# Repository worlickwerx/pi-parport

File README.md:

## pi-parport

This is a Raspberry Pi HAT that implements a PC-style parallel port.
GPIO pins are organized as data, status, and control registers.
The HAT includes a buffer chip that converts from the GPIB 3V3 logic
to signals that conform to IEEE 1284.  A 26 pin IDC header on the
board connects to your DB25 connector.  A `parport-gpio` driver and
device tree overlay integrate the HAT with the Linux parport driver stack.

### Why?

I wanted to use a parallel port based cooled astronomy camera,
but preferred to use the compact and low-power Raspberry Pi
over a PC at the telescope.  Parallel ports are simple devices.
Why not build one?

### What works?

See [wiki](https://github.com/worlickwerx/pi-parport/wiki) for notes on some
devices, and please share your experience if you try something new.

The following limitations of this implementation may affect software and
hardware that uses the parallel port:
1) The software cannot directly read and write the x86 port addresses,
as was the custom early on.  In user space, software must use the ppdev
ioctl interface.  In the kernel, software must use the (generic)
`struct parport` operations.
2) The GPIO multiplexing/de-multiplexing and/or system call access may
impact the direct-access latency assumed by some bit-banged drivers.
On a Pi 3, user space code can toggle a parallel port line at about 250 kHz.
3) Bidirectional control pins are not currently supported, but bidirectional
data pins are supported.  There are alternatives to the current buffer chip
that would support this, but they require a slightly more complicated
circuit.

### Why not use a USB Parallel Port?

Many USB parallel port devices appear to Linux as a USB printer, bypassing
the parport driver stack.  If your application is a printer, go for it.

### Building the driver

For convenience, the generic parport code is duplicated in this repo,
since the Raspberry Pi Foundation does not ship the compiled modules
in the `raspberrypi-kernel` package (at least in old Raspbian
versions).  If you are intending to use a specific old version of
Raspbian, there is the shell script `get_parport_src.sh` to assist
you in getting the code from that particular version.

Clone this repo, then run the following with `${TOPDIR}` representing the
top level directory of the cloned repo:
```console
$ sudo apt install build-essential raspberrypi-kernel-headers
$ cd ${TOPDIR}/driver
$ make
make -C /lib/modules/4.19.75-v7+/build M=${TOPDIR}/driver modules
make[1]: Entering directory '/usr/src/linux-headers-4.19.75-v7+'
  CC [M]  ${TOPDIR}/driver/parport/share.o
  CC [M]  ${TOPDIR}/driver/parport/ieee1284.o
  CC [M]  ${TOPDIR}/driver/parport/ieee1284_ops.o
  CC [M]  ${TOPDIR}/driver/parport/procfs.o
  CC [M]  ${TOPDIR}/driver/parport/daisy.o
  CC [M]  ${TOPDIR}/driver/parport/probe.o
  LD [M]  ${TOPDIR}/driver/parport/parport.o
  CC [M]  ${TOPDIR}/driver/parport/lp.o
  CC [M]  ${TOPDIR}/driver/parport/ppdev.o
  CC [M]  ${TOPDIR}/driver/parport_gpio.o
  Building modules, stage 2.
  MODPOST 4 modules
  CC      ${TOPDIR}/driver/parport/lp.mod.o
  LD [M]  ${TOPDIR}/driver/parport/lp.ko
  CC      ${TOPDIR}/driver/parport/parport.mod.o
  LD [M]  ${TOPDIR}/driver/parport/parport.ko
  CC      ${TOPDIR}/driver/parport/ppdev.mod.o
  LD [M]  ${TOPDIR}/driver/parport/ppdev.ko
  CC      ${TOPDIR}/driver/parport_gpio.mod.o
  LD [M]  ${TOPDIR}/driver/parport_gpio.ko
make[1]: Leaving directory '/usr/src/linux-headers-4.19.75-v7+'
```

### Installing the Device Tree Overlay

The device tree overlay maps specific GPIO pins to their functions in
the driver.  This must be compiled and loaded:
```console
$ cd ${TOPDIR}/dts
$ make
$ sudo make install
```
The ID EEPROM stores the name of the DT Overlay to use, and the
corresponding DT Overlay will be automatically loaded on boot.  If you
will not be using an ID EEPROM, then add the following line to
`/boot/config.txt`:
```
dtoverlay=parport-gpio
```
The default drive mode of the parallel port output pins is
"totem-pole" mode, which means that a high current source is provided
for both logic level 1 and 0.  If you wish logic level 1 to be a low
current source provided by pull-up resistors, i.e. "open-drain" mode,
then you can set the following DT Overlay parameter:
```
dtoverlay=parport-gpio,hd=0
```
Note that if you are using an EEPROM, you will have to include the
full DT Overlay data within your EEPROM since you cannot simply
specify a parameter when loading by that method.

Then reboot the pi to pick up the new config.

### Installing the Modules

Install the modules to allow Linux Device Tree to automatically load
them.
```console
$ cd ${TOPDIR}/driver
$ sudo make install
```
Note that only the `parport` and `parport_gpio` base modules will
autoload, the `ppdev` and `lp` modules will still need to be specified
in `/etc/modules` or otherwise.  Also, note that you will need to
rebuild and reinstall the modules when you update your kernel version.

### Loading the Modules

If you did not install the modules, after rebooting, load the base
modules like this:
```console
$ cd ${TOPDIR}
$ sudo insmod driver/parport/parport.ko
$ sudo insmod driver/parport_gpio.ko
```
You'll see the port announce itself on the console:
```console
[4425200.988400] parport-gpio ppgpio@0: data on pins [22,23,24,10,25,9,8,11]
[4425200.988412] parport-gpio ppgpio@0: status on pins [18,17,4,3,2]
[4425200.988422] parport-gpio ppgpio@0: control on pins [26,19,6,13]
[4425200.988430] parport-gpio ppgpio@0: hd on pin 20
[4425200.988438] parport-gpio ppgpio@0: dir on pin 21
```
If you wish to set up a parallel printer:
```console
$ sudo insmod parport/lp.ko
```
If you wish to run user-space programs that use the parallel port:
```console
$ sudo insmod parport/ppdev.ko
```

### hardware

The latest hardware includes an ID EEPROM to conform with the
[Raspberry Pi HAT Specification](https://github.com/raspberrypi/hats),
and was designed with [KiCAD](https://www.kicad.org/).
As with the previous versions, the
[SN74LVC161284 19-bit bus interface with 3-state outputs](http://www.ti.com/product/SN74LVC161284) takes care of buffering and line conditioning.

Version 4 is shared on
[OSHPARK](https://oshpark.com/shared_projects/0Ioh20Gk).
See the [Bill of Materials](hardware/v4/BOM.md) for parts to place on
the board.

Populating the EEPROM and associated components on a board you're making
yourself is optional.

Check out the [test](test/) directory for some simple "smoke tests"
on your assembled pi-parport board before attaching your more
expensive equipment.

Schematics and design files for [previous versions](hardware/)
are still available for reference.

### Release

Share and enjoy!

#### Software License

SPDX-License-Identifier: GPL-2.0-or-later

#### Hardware License

SPDX-License-Identifier: CERN-OHL-1.2

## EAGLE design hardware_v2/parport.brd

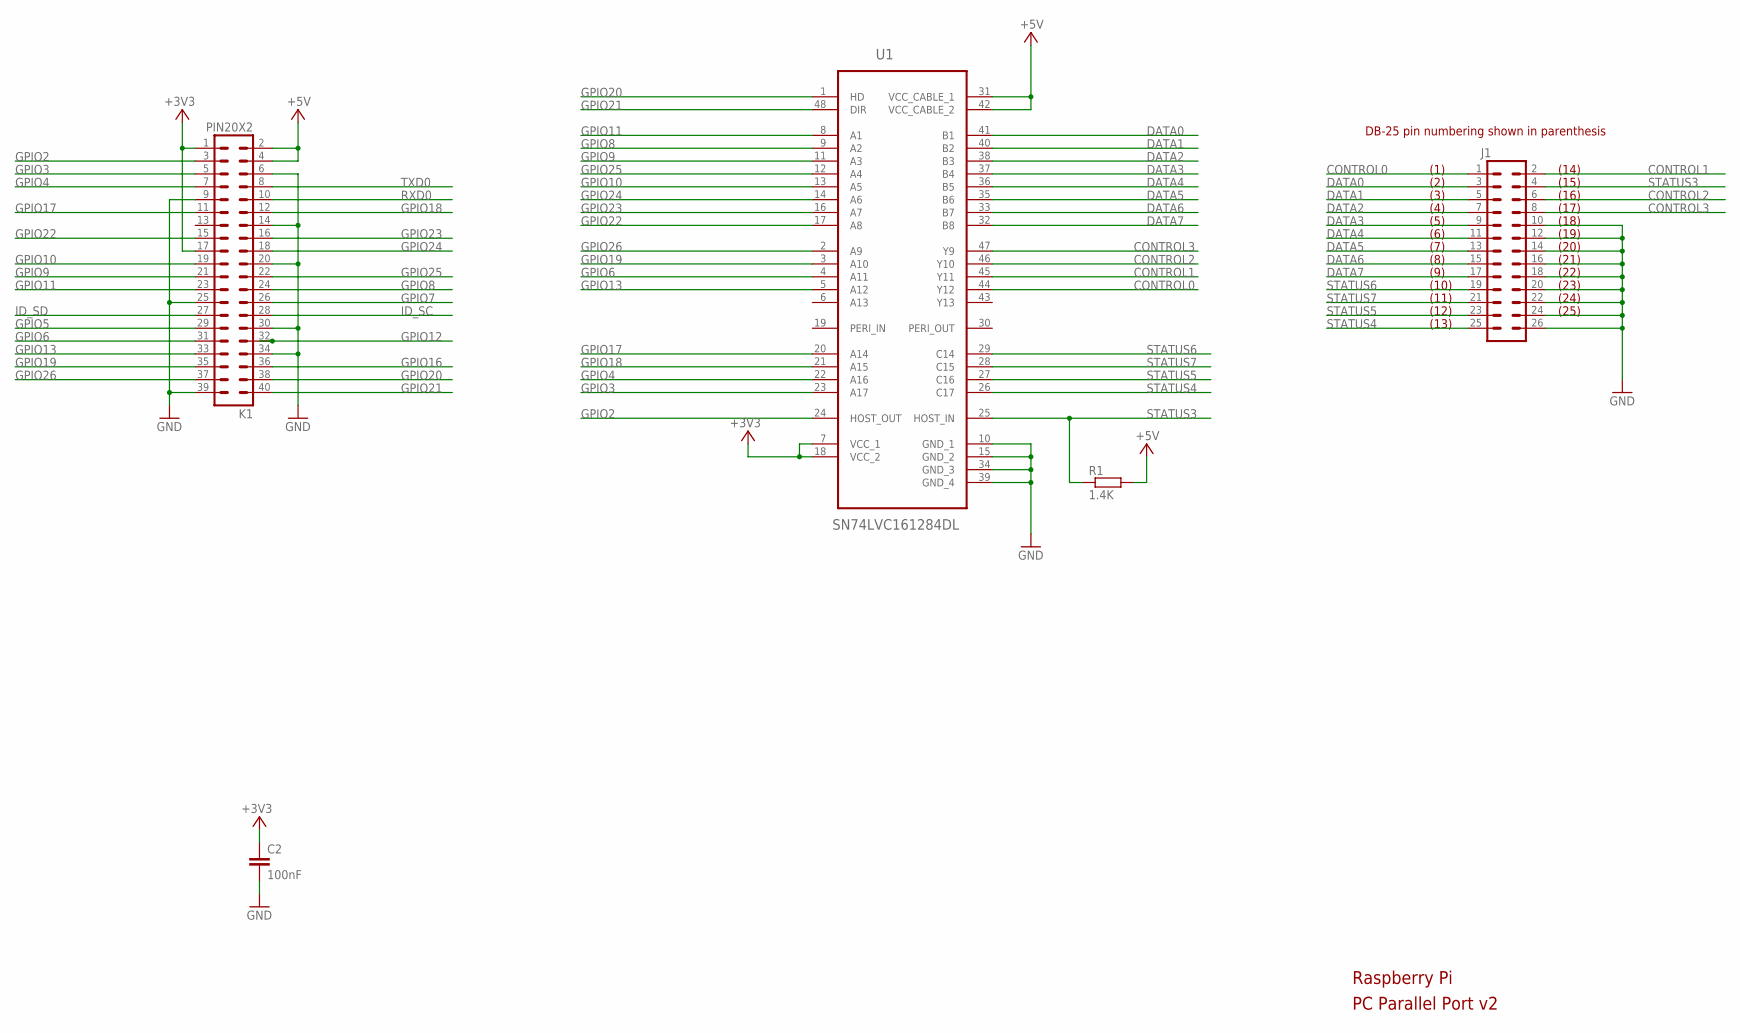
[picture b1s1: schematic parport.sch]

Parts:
C2: 100nF; C0805
J1: M13X22X13; 2X13
K1: PIN20X2; PIN_20X2
R1: 1.4K; R0805
U1: SN74LVC161284DL; SOP63P1035X279-48N

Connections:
+3V3: C2.1, K1.1, K1.17, U1.7 (VCC_1), U1.18 (VCC_2)
+5V: K1.2, K1.4, R1.2, U1.31 (VCC_CABLE_1), U1.42 (VCC_CABLE_2)
CONTROL0: J1.1, U1.44 (Y12)
CONTROL1: J1.2, U1.45 (Y11)
CONTROL2: J1.6, U1.46 (Y10)
CONTROL3: J1.8, U1.47 (Y9)
DATA0: J1.3, U1.41 (B1)
DATA1: J1.5, U1.40 (B2)
DATA2: J1.7, U1.38 (B3)
DATA3: J1.9, U1.37 (B4)
DATA4: J1.11, U1.36 (B5)
DATA5: J1.13, U1.35 (B6)
DATA6: J1.15, U1.33 (B7)
DATA7: J1.17, U1.32 (B8)
GND: C2.2, J1.10, J1.12, J1.14, J1.16, J1.18, J1.20, J1.22, J1.24, J1.26, K1.6, K1.9, K1.14, K1.20, K1.25, K1.30, K1.34, K1.39, U1.6 (A13), U1.10 (GND_1), U1.15 (GND_2), U1.19 (PERI_IN), U1.34 (GND_3), U1.39 (GND_4)
GPIO2: K1.3, U1.24 (HOST_OUT)
GPIO3: K1.5, U1.23 (A17)
GPIO4: K1.7, U1.22 (A16)
GPIO5: K1.29
GPIO6: K1.31, U1.4 (A11)
GPIO7: K1.26
GPIO8: K1.24, U1.9 (A2)
GPIO9: K1.21, U1.11 (A3)
GPIO10: K1.19, U1.13 (A5)
GPIO11: K1.23, U1.8 (A1)
GPIO12: K1.32
GPIO13: K1.33, U1.5 (A12)
GPIO16: K1.36
GPIO17: K1.11, U1.20 (A14)
GPIO18: K1.12, U1.21 (A15)
GPIO19: K1.35, U1.3 (A10)
GPIO20: K1.38, U1.1 (HD)
GPIO21: K1.40, U1.48 (DIR)
GPIO22: K1.15, U1.17 (A8)
GPIO23: K1.16, U1.16 (A7)
GPIO24: K1.18, U1.14 (A6)
GPIO25: K1.22, U1.12 (A4)
GPIO26: K1.37, U1.2 (A9)
ID_SC: K1.28
ID_SD: K1.27
RXD0: K1.10
STATUS3: J1.4, R1.1, U1.25 (HOST_IN)
STATUS4: J1.25, U1.26 (C17)
STATUS5: J1.23, U1.27 (C16)
STATUS6: J1.19, U1.29 (C14)
STATUS7: J1.21, U1.28 (C15)
TXD0: K1.8

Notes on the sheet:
Raspberry Pi
PC Parallel Port v2
(1)
(2)
(3)
(4)
(5)
(6)
(7)
(8)
(9)
(10)
(11)
(12)
(13)
(14)
(15)
(17)
(18)
(19)
(20)
(21)
(22)
(23)
(24)
(25)
(16)
DB-25 pin numbering shown in parenthesis

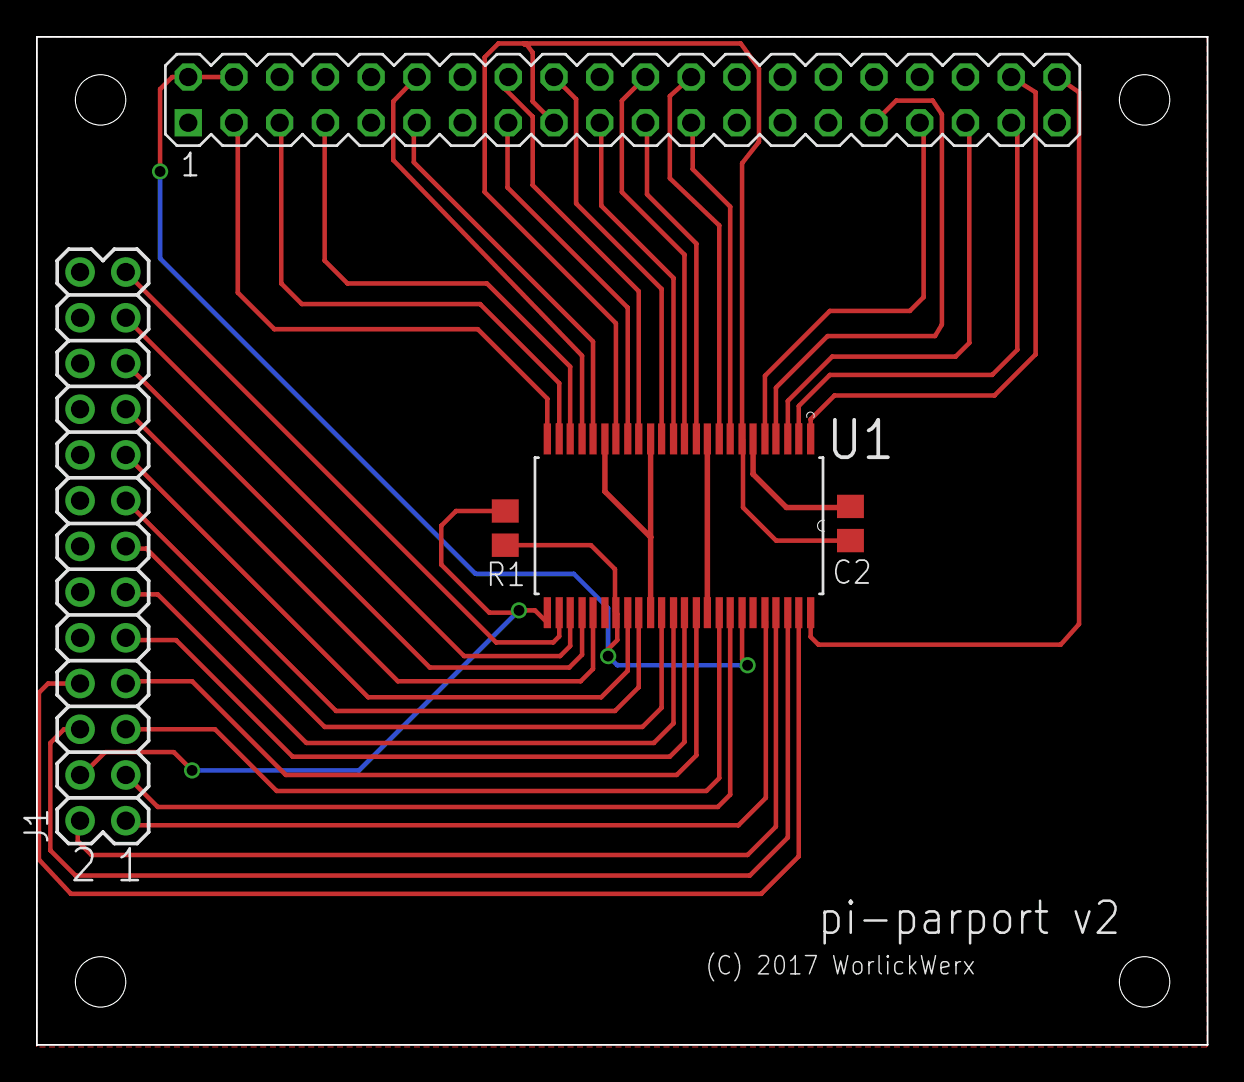
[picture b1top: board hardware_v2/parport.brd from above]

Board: 2 copper layers, 65.0 x 56.0 mm, 5 parts (0 on the bottom side), 39 nets.

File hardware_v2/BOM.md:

## hardware v2 bill of materials

| Quan | Part no | Manuf part no | Description | Package | Supplier | Notes |
| ---- | ------- | ------------- | ----------- | ------- | -------- | ----- |
| 1    | U1      | [SN74LVC161284DLR](http://www.ti.com/product/SN74LVC161284) | 19-bit bus interface with 3-state outputs | SSOP (0.64mm lead pitch) | [Arrow Electronics](https://www.arrow.com/en/products/sn74lvc161284dlr/texas-ins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 | pin 1 marking oriented opposite J1 |
| 1    | R1      |               | 1.4K ohm, 1/8 watt resistor              | 0805 |     | Pull-up for STATUS3 |
| 1    | C2      |               | 100nF, 50V capacitor                     | 0805 |     | Bypass |
| 1    | J1      |               | 13x2 male header                         | through-hole (2.54mm pitch) |    | Straight or 90 degree depending on application |
| 1    | K1      |               | 20x2 female header                       | through-hole (2.54mm pitch) | [Adafruit](https://www.adafruit.com/product/2222) | pi GPIO header |
| 4    |         |               | M2.5 x 16mm brass standoff, with M2.5 nut |                            | [Adafruit](https://www.adafruit.com/product/2336) | pi HAT standoff (height 11mm) |
| 4    |         |               | M2.5 x 6mm philips head screw            |     |    |    |
| 1    |         |               | Female DB25 to female 13x2 header cable assembly |     | [Amazon](https://www.amazon.com/Motherboard-Parallel-Printer-bracket-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 | or surplus |

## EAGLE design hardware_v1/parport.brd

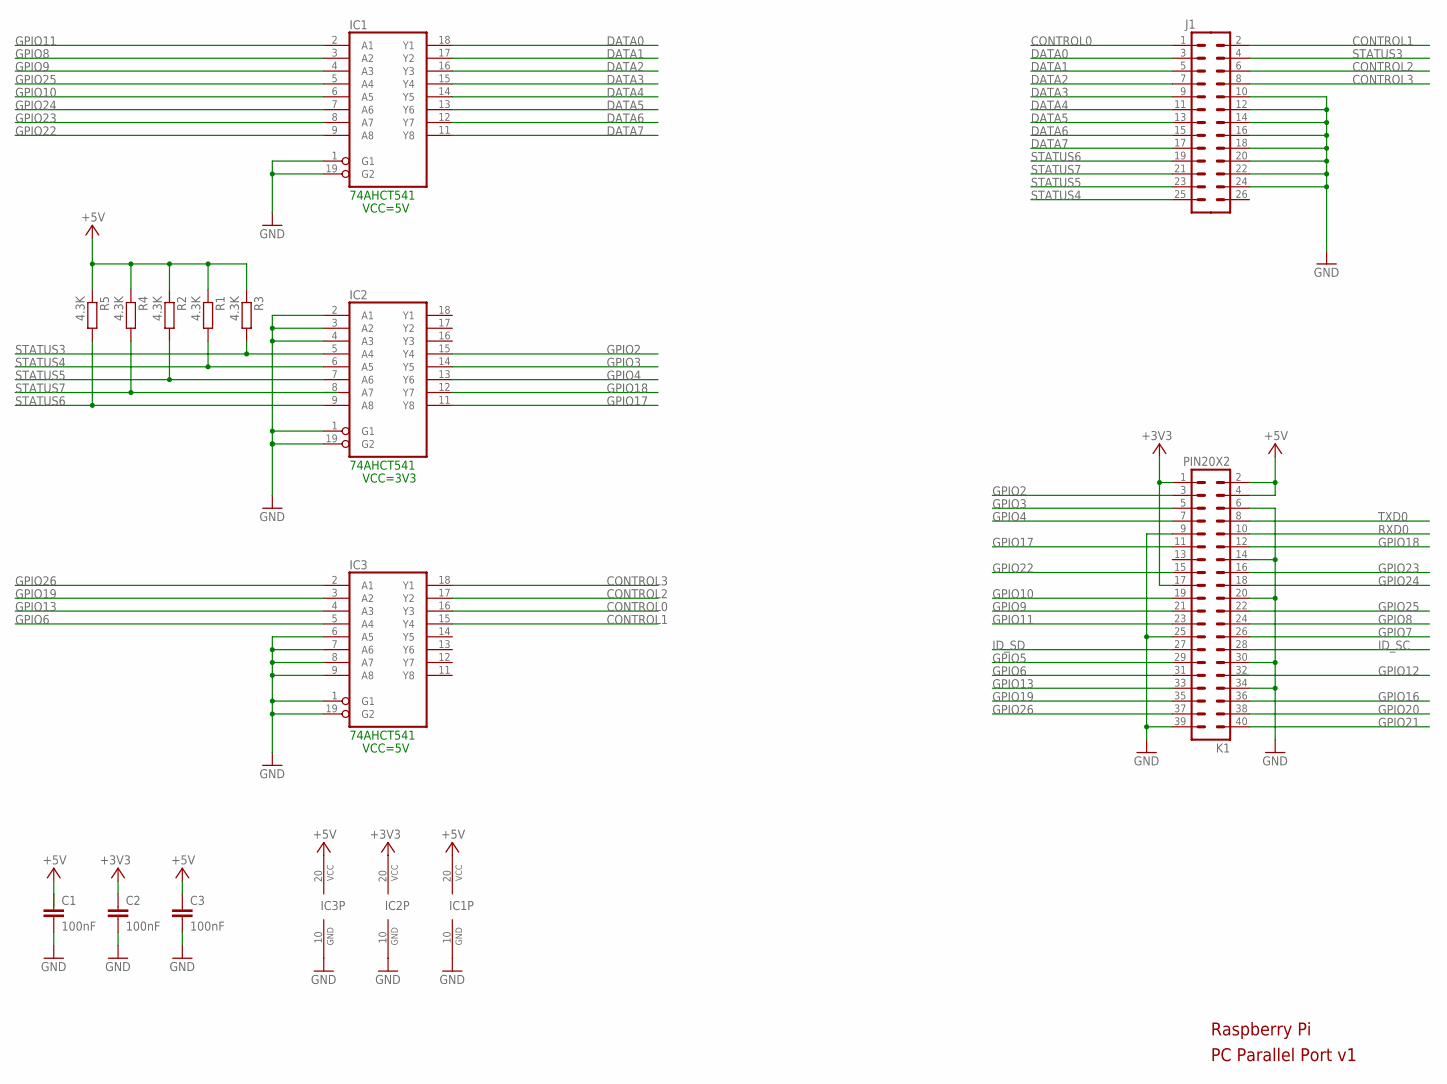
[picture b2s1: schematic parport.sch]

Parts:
C1, C2, C3: 100nF; C0805
IC1, IC2, IC3: 74LS541DW; SO20W
J1: M13X22X13; 2X13
K1: PIN20X2; PIN_20X2
R1, R2, R3, R4, R5: 4.3K; R0805

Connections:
+3V3: C2.1, IC2.20 (VCC), K1.1, K1.17
+5V: C1.1, C3.1, IC1.20 (VCC), IC3.20 (VCC), K1.2, K1.4, R1.1, R2.1, R3.1, R4.1, R5.1
CONTROL0: IC3.16 (Y3), J1.1
CONTROL1: IC3.15 (Y4), J1.2
CONTROL2: IC3.17 (Y2), J1.6
CONTROL3: IC3.18 (Y1), J1.8
DATA0: IC1.18 (Y1), J1.3
DATA1: IC1.17 (Y2), J1.5
DATA2: IC1.16 (Y3), J1.7
DATA3: IC1.15 (Y4), J1.9
DATA4: IC1.14 (Y5), J1.11
DATA5: IC1.13 (Y6), J1.13
DATA6: IC1.12 (Y7), J1.15
DATA7: IC1.11 (Y8), J1.17
GND: C1.2, C2.2, C3.2, IC1.1 (G1), IC1.10 (GND), IC1.19 (G2), IC2.1 (G1), IC2.2 (A1), IC2.3 (A2), IC2.4 (A3), IC2.10 (GND), IC2.19 (G2), IC3.1 (G1), IC3.6 (A5), IC3.7 (A6), IC3.8 (A7), IC3.9 (A8), IC3.10 (GND), IC3.19 (G2), J1.10, J1.12, J1.14, J1.16, J1.18, J1.20, J1.22, J1.24, K1.6, K1.9, K1.14, K1.20, K1.25, K1.30, K1.34, K1.39
GPIO2: IC2.15 (Y4), K1.3
GPIO3: IC2.14 (Y5), K1.5
GPIO4: IC2.13 (Y6), K1.7
GPIO5: K1.29
GPIO6: IC3.5 (A4), K1.31
GPIO7: K1.26
GPIO8: IC1.3 (A2), K1.24
GPIO9: IC1.4 (A3), K1.21
GPIO10: IC1.6 (A5), K1.19
GPIO11: IC1.2 (A1), K1.23
GPIO13: IC3.4 (A3), K1.33
GPIO16: K1.36
GPIO17: IC2.11 (Y8), K1.11
GPIO18: IC2.12 (Y7), K1.12
GPIO19: IC3.3 (A2), K1.35
GPIO20: K1.38
GPIO21: K1.40
GPIO22: IC1.9 (A8), K1.15
GPIO23: IC1.8 (A7), K1.16
GPIO24: IC1.7 (A6), K1.18
GPIO25: IC1.5 (A4), K1.22
GPIO26: IC3.2 (A1), K1.37
ID_SC: K1.28
ID_SD: K1.27
RXD0: K1.10
STATUS3: IC2.5 (A4), J1.4, R3.2
STATUS4: IC2.6 (A5), J1.25, R1.2
STATUS5: IC2.7 (A6), J1.23, R2.2
STATUS6: IC2.9 (A8), J1.19, R5.2
STATUS7: IC2.8 (A7), J1.21, R4.2
TXD0: K1.8

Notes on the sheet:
Raspberry Pi
PC Parallel Port v1
74AHCT541
VCC=5V
VCC=3V3

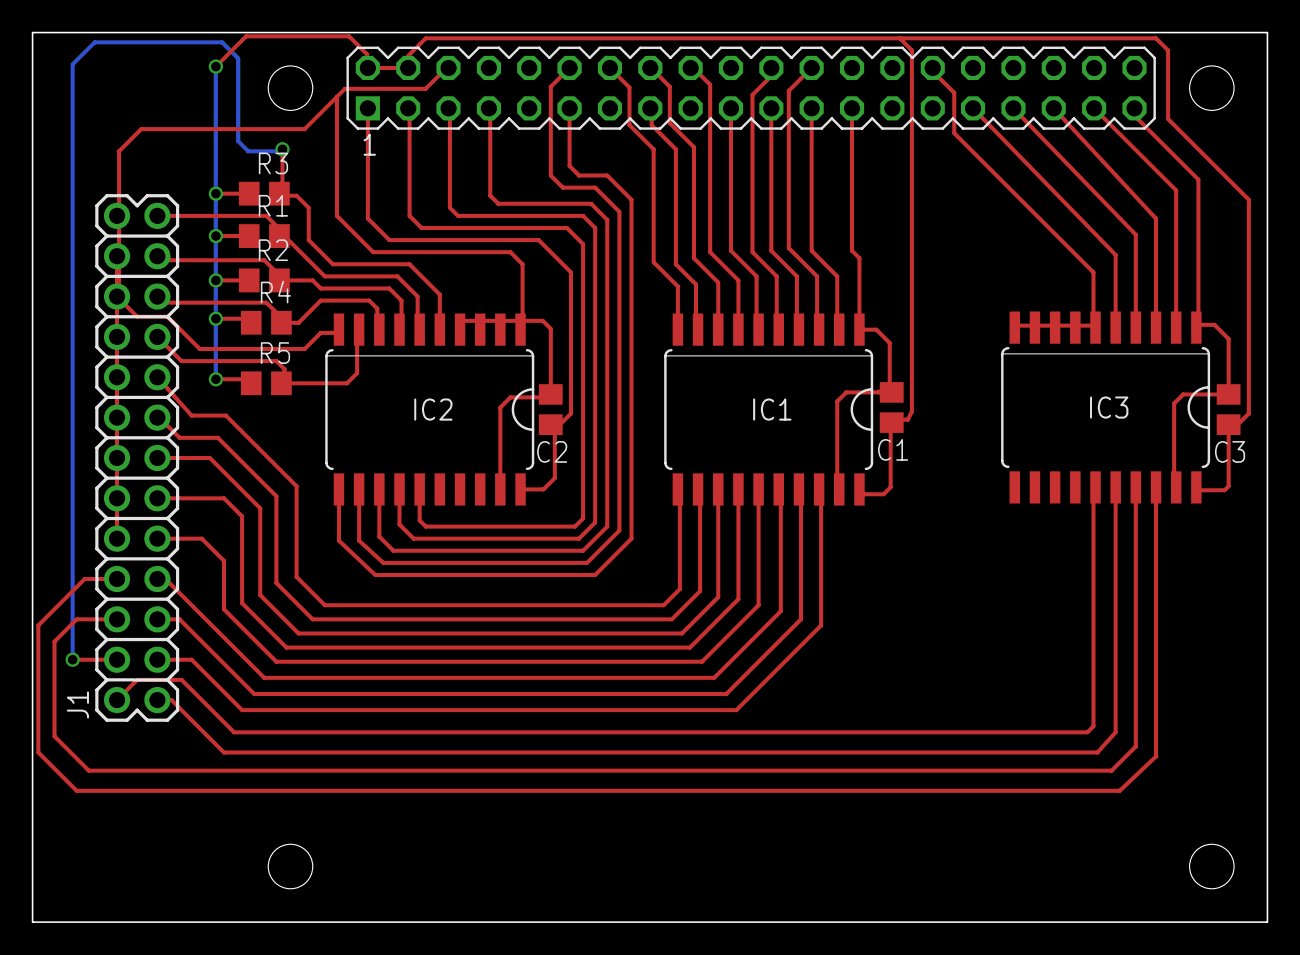
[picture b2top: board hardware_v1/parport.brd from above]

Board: 2 copper layers, 77.7 x 56.0 mm, 13 parts (0 on the bottom side), 37 nets.

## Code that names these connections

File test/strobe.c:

// SPDX-License-Identifier: GPL-2.0-or-later

/* strobe - pulse specified pin for scope */

#include <stdio.h>
#include <sys/ioctl.h>
#include <linux/parport.h>
#include <linux/ppdev.h>
#include <fcntl.h>
#include <time.h>
#include <unistd.h>
#include <stdlib.h>
#include <stdarg.h>
#include <errno.h>
#include <string.h>

#define DEVICE_PATH "/dev/parport0"

void die (const char *fmt, ...)
{
    va_list ap;

    va_start (ap, fmt);
    (void)vfprintf (stderr, fmt, ap);
    va_end (ap);
    exit (1);
}

void say (const char *fmt, ...)
{
    va_list ap;

    va_start (ap, fmt);
    (void)vfprintf (stderr, fmt, ap);
    va_end (ap);
}

void usage (void)
{
    fprintf (stderr, "Usage: strobe pin\n");
    fprintf (stderr, "where pin is DATA0, DATA1, CONTROL0, CONTROL1...\n");
    exit (1);
}

/* measured 253khz in a tight loop on pi3 */
void strobe (int fd, const char *pin)
{
    unsigned char out;
    unsigned long request;
    int bit;
    int count;

    if (!strncmp (pin, "DATA", 4)) {
        bit = atoi (pin + 4);
        if (bit < 0 || bit > 7)
            usage ();
        request = PPWDATA;
    }
    else if (!strncmp (pin, "CONTROL", 7)) {
        bit = atoi (pin + 7);
        if (bit < 0 || bit > 4)
            usage ();
        request = PPFCONTROL;
    }
    else
        usage ();

    for (count = 0; ; count++) {
        if (request == PPWDATA) {
            unsigned char out = (count % 2) ? 0 : (1<<bit);

            if (ioctl (fd, request, &out) < 0)
                die ("ioctl PPWDATA: %s\n", strerror (errno));
        }
        else {
            struct ppdev_frob_struct frob = {
                .mask = 1<<bit,
                .val = (count % 2) ? 0 : (1<<bit),
            };
            if (ioctl (fd, request, &frob) < 0)
                die ("ioctl PPFCONTROL: %s\n", strerror (errno));
        }
    }
}

int main (int argc, char *argv[])
{
    int fd, mode, dir;
    const char *pin;
    int rc;

    if (argc != 2)
        usage ();
    pin = argv[1];

    fd = open (DEVICE_PATH, O_RDWR);
    if (fd < 0)
        die ("%s: %s\n", DEVICE_PATH, strerror (errno));
    if (ioctl (fd, PPCLAIM, NULL) < 0)
        die ("ioctl PPCLAIM: %s\n", strerror (errno));

    mode = IEEE1284_MODE_BYTE;
    if (ioctl (fd, PPSETMODE, &mode) < 0)
        die ("ioctl PPSETMODE IEEE1284_MODE_BYTE: %s\n", strerror (errno));

    dir = 0;
    if (ioctl (fd, PPDATADIR, &dir) < 0)
        die ("ioctl PPDATADIR 0 (out): %s\n", strerror (errno));

    strobe (fd, pin);

    if (ioctl (fd, PPRELEASE) < 0)
        die ("ioctl PPRELEASE: %s\n", strerror (errno));
    if (close(fd) < 0)
        die ("close %s: %s\n", DEVICE_PATH, strerror (errno));

   return rc;
}

/*
 * vi:tabstop=4 shiftwidth=4 expandtab
 */

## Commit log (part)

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2017-06-25 hardware_v1: add initial prototype hardware
    This is a pi HAT (not officially: no EEPROM, wrong size) that
    has a DB25 on it and three 74AHCT541 8-channel buffers for
    3V3/5V level conversion. Pi GPIOs are mapped directly to
    parallel port data, status, and control lines. It should be
    adequate for SPP mode.
    It's layed out as a single sided board since that's easier for
2017-06-25 README: add project readme
2017-07-30 dts: add device tree overlay
    Add initial device tree overlay for parport-gpio module
    to identify and provide initial config for GPIO pins assigned
    to data, status, and control ports.
    The "compatible" name links the driver and the dts file.
    On the pi, after the compiled dtbo file is installed,
    add the following to /boot/config.txt:
2017-07-30 driver: pull in the rest of the parport stack
    Since the Pi Foundation isn't likely to configure the parport
    stack in their default kernel anytime soon, pull in the bits
    here so they can be built out of tree with the parport-gpio
    module, thus making it a bit easier to get started.
    insmod parport.ko
    insmod parport_gpio.ko
2017-08-05 hardware_v1: status 10k pd -> 4.3k pu
    Change the 10K pulldowns to 4.3K pullups.
    4.7K is what would normally be used here but I had some
    803 4.3K's on hand.
    Place some vias for the pullups and also for the unrouted
    CONTROL3 line. Before we had a one sided board which is
    a bit easier to fab with the CNC. Place vias so it can
2017-08-06 hardware_v1: include DB-25 pin numbering on schematic
2017-08-06 driver: fix NULL oops
    If CONFIG_PARPORT_NOT_PC is not defined and CONFIG_PARPORT_1284
    is defined, internal 1284 "daisy" probing causes a NULL pointer
    dereference (oops) at insmod of parport_gpio.ko.
    This is likely due to a conditional in parport.h that, if NOT_PC
    is undefined, hardwires operations to the PC versions, bypassing
    the operations table. I did not run down why the hardwired
2017-08-06 README.md: fix typos
2017-08-06 driver: delete port on module unload
    Call parport_del_port() instead of parport_put_port()
    when the module is unloaded, so that parport0 can be
    reused if the module is re-loaded. Otherwise we get
    parport1, 2, and so on.
    Also, change printk code so the port number is displayed
    with the assigned GPIO pins e.g.
2017-08-06 driver: fix polarity in parport_gpio_read_control()
    In parport_gpio_read_control(), it is necessary to invert
    some of the control bits that are supposed to be active low.
2017-08-06 driver: optimize frob_control operation
    Write bits individually if present in the mask rather than
    doing it in bulk as if we were dealing with actual I/O ports.
    Fixes #5
2017-08-06 README.md: note the upstream code pulled in
2017-08-07 driver: stop using raw gpiod interface
    In the dts file expression <&gpio n m>, n is the pin and m
    is the polarity, not direction. If m=0, the pin is active
    high; if m=1, active low.
    Set all the pins active high and then stop using
    the "raw" gpiod interfaces to access them.
    Fixes #3
2017-08-13 dts: [cosmetic] fix comments and formatting
2017-08-24 test/cableTest2: add simple ppdev based cable test
    Add a simple parallel port cable test that toggles
    the data lines from user space via ppdev.
    Credit: Dr. Andrew Greensted
    http://www.labbookpages.co.uk/electronics/parallelPort.html
2017-10-22 hardware_v2: add pdfs
2017-10-22 hardware_v2: fix drc errors, add silk title
    This version ordered from OSH Park (3 boards).
2017-12-04 driver: support hd and dir pins for v2 hardware
    In the v2 hardware design, hd and dir are pins on the
    SN74LVC161284 19-bit bus interface that determine the
    drive mode (1=totem pole, 0=open drain) and data port
    direction (1=AtoB, 0=BtoA).
    If the device tree overlay defines them, initialize
    both pins to 1.
2017-12-08 test/loop: add loopback test
2018-07-09 driver: update some includes
    Problem: compilation errors with latest rpi kernel
    headers (1.20180703-1), in generic parport, ppdev, lp code.
    This really should be synced with upstream kernel sources,
    but an initial check didn't reveal any changes to the parport
    stuff. For now, adjust includes to avoid compilation errors.
2018-07-11 README.md: add oshpark link
2018-09-09 hardware_v2: add bill of materials
2019-04-27 driver/parport: move upstream copies to parport dir
    Problem: parport module code that the rpi foundation doesn't
    configure into their kernel, but which is required by parport-gpio,
    was copied into our repo. But it's not clear what's the new code
    and what's copied kernel code.
    Move the copied kernel code into the parport subdir.
2019-04-27 driver: [style] add missing blank line after decls
    Address checkpatch warning:
    WARNING: Missing a blank line after declarations
2019-04-27 driver: [style] drop extra oom message
    Address checkpatch warning:
    WARNING: Possible unnecessary 'out of memory' message
    See also: https://lkml.org/lkml/2014/6/10/382
2019-04-27 driver: [style] fix malformed SPDX-License-Identifier
    Address checkpatch warning:
    WARNING: Missing or malformed SPDX-License-Identifier tag in line 1
2019-04-27 driver: [style] reformat with clang-format
    Add .clang-format from source and run
    clang-format -i parport_gpio.c
    to automatically fix as many kernel style issues as
    possible in one go.
2019-04-27 driver: add make check target that runs checkpatch
    Run the kernel style checker in response to 'make check'.
2019-04-27 README.md: update console output
    Switching to the dev_{level} printk macros causes some
    minor changes in the expeced console output, so update
    the README.md example output.
2019-08-04 drivers/parport: update source to track raspbian
    Problem: parport code fails to compile after raspbian update
    to 4.19.57-v7+ kernel.
    Update parport code that we copied into this project from
    the kernel source, needed until pi kernel maintainers enable
    the parallel port code in their configuration (not very likely).
    Code copied from master branch of:
2020-01-02 hardware_v3: rework v2 in KiCAD
    Create a new hardware version with the following changes
    1) Use KiCAD instead of Eagle so that other people can
    more easily modify/remix.
    2) Add HAT EEPROM to conform to Pi Foundation specs
    3) OSHW logo on board
    After I sent this to OSHPARK I realized I omitted the
2020-01-02 hardware_v3: add schematic pdf
2020-01-02 test/loop: add second loopback pinout
    Call the ebay plug "Plug A".
    Refactor to allow the type of plug and the number of
    iterations to be specified on the command line.
    Add "Plug B" with pinout designed to cover pins not
    covere by "Plug A".
2020-01-02 test/walk: drop test
    With a second loopback plug, there is no longer any
    need for the "walk" test.
2020-01-02 test/loop: add SPDX license reference
2020-01-02 README.md: move old versions to hardware_old
2020-01-02 README.md: add OSHAPRK link
2020-01-03 eeprom: add notes and Makefile to flash EEPROM
    Verify that the EEPROM hardware works by flashing a
    board identity in there.
    Fixes #26
2020-03-12 hardware_v3: add BOM manufacturer part numbers
2020-03-12 hardware_v3: also add package, description, notes fields for BOM
2020-03-13 hardware_v3: fix BOM table heading
2020-06-20 driver: skip parport if KERNEL_HAS_PARPORT defined
2020-07-26 Rearrange hardware repo structure.
2020-07-26 hardware: add generated media
2020-07-26 hardware_v4: add bypass capacitors, reroute traces
    Do not route trace under resistor R5. Move U2 upward to facilitate
    rerouting this trace without adding more vias.
    Also make sure footprints between schematic and PCB are in sync.
    Update BOM with new parts.
    Hardware version needs to be bumped due to PCB changes. Version numbers
    in schematic and PCB source changed, new files will need to be generated
2020-07-26 hardware: no symlinks for Markdown images on GitHub
2020-08-11 hardware: BOM improvements/fixes.
    * Fix capacitor quantity in v4.
    * SN74LVC161284DLR Digi-Key part number: cut tape packaging
    discontinued at Digi-Key, use tube packaging instead.
    * Fix 40-pin and 26-pin headers, accidentally picked 2 mm pitch parts
    instead of 2.54 mm pitch parts.
2020-10-18 Update gpiod_set_array_value call to new contract.
2020-10-23 Correct error in README.md.
2020-10-23 driver: Forwards and backwards compatibility with Linux versions.
    Also make corresponding improvements to the READMEs.
    Fix a few checkpatch.pl warnings recently introduced, while at the same
    time introducing four checkpatch.pl warnings due to conditional
    compilation on the Linux version.
2020-11-01 Remove trailing whitespace accidentally added to README.md.
2020-11-11 dts, driver: Add DT Overlay parameter for drive mode.
2021-01-02 hardware: Add DIP jumper to BOM.
2021-01-05 README: point to v4 board + BOM, not v3
    Problem: the top level README.md still points to the v3 board
    on oshpark.
    Change it to point to the v4 board, and update the BOM reference
    to v4 as well.
2021-01-06 ci: add driver builds
    Add jobs to the main github workflow that install kernel headers
    and build the driver for:
    - Ubuntu 20.04 / linux 5.4.0
    - Ubuntu 18.04 / linux 4.15.0
    - Ubuntu 16.04 / linux 4.4.0
2021-01-06 ci: invoke pr-validator on PRs
    Add a 'main' github workflow containing one 'job',
    that validates PRs, ensuring that:
    - commit messages conform to line length recommendations
    - commit subjects don't include "fixup" or "squash"
    - there are no merge commits
    The validator script was shared from:
2021-11-12 ci: drop ubuntu-16.04 / linux-4.4 build
    Problem: CI workflow hangs waiting for nonexistent runner type.
    Github has deprecated the ubuntu-16.04 runner.
    Drop the ubuntu-16.04 / linux-4.4 build.
2021-11-12 ci: load the driver
    Problem: CI does not catch errors that occur when the
    driver is loaded.
    Add a test that builds the driver against the running kernel
    and loads it.
2021-11-14 driver/parport: sync with linux-5.10
    Problem: vendored copy of parport code no longer compiles
    on raspbian kernel 5.10.63-v7+ due to kernel API changes.
    Pull in the latest copy of parport source from linux-5.10.
    There are no local modifications.
2024-09-01 v5: update page settings
    Problem: template pages are A4 size and have have boiler plate
    metadata.
    Switch to U.S. letter size and update page metadata with project
    specific info.
2024-09-17 v5: import/reimplement parport design on template
    Problem: template board is still blank.
    Adjust board edge to handle SMT header and add cutout for pi5 camera/
    display FFC connectors. For GPIO connector, use existing kicad 8 Harwin
    M20 series footprint but adjust the pinout for top of board pi GPIO,
    and adjust position since centroid moved from THT pin 1 to SMT centroid.
    Add keepout for pi5 PoE like the existing one for pi4.
2024-09-21 ci: update checkout action to v4 to silence warnings
    Problem: github issues warnings when it runs our ci:
    The following actions uses node12 which is deprecated and will
    be forced to run on node16: actions/checkout@v2.
    Switch to v4.
2024-09-21 ci: add github action to check v5 ERC/DRC
    Problem: new PR's that change board design files should be
    automatically checked.
2024-09-22 build: add script to generate gerbers
    Problem: we need gerbers for the fab house.
    Add a script to generate gerbers as a zip file.
    Add a Makefile target for the v5 board.
2024-09-22 v5: add BOM data needed for JLCPCB assembly
    Problem: component metadata is not in a form that could be sent
    out for assembly.
    Add BOM fields recommended for JLCPCB assembly[1] and fill in.
    [1] https://jlcpcb.com/help/article/How-to-generate-the-BOM-and-Centroid-file-from-KiCAD
2024-09-22 build: add script to generate BOM csv file
    Problem: we need a csv file to send to the board assembly house.
    Add a script to generate it and a Makefile target for the v5 board.
2024-10-03 v5: enlarge 2x20 header alignment holes
    Problem: 2x20 header alignment holes for Harwin M20 are 1.8mm dia.
    The LCSC replacement requires 2mm dia alignment holes.
    Update footprint and board.
2024-10-03 v5: switch J4 to SMT
    Problem: the J4 1x3 header is a through hole part that is marked
    "do not place" so it can be installed by hand.
    Switch J4 to an SMT footprint and uncheck DNP.
    Adjust board routing.
    Add a LCSC part number to the BOM.
2024-10-04 v5: remove some DRC exclusions
    Problem: DCR excludes "holes inside courtyard" for some reason.
    These checks pass so may as well enable them.

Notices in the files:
hardware_v2/parport.brd:
(C) 2017 WorlickWerx
parts and their libraries:
SparkFun-Connectors: Licensing: Creative Commons ShareAlike 4.0 International - https://creativecommons.org/licenses/by-sa/4.0
